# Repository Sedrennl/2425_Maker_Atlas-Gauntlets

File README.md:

# 🛠️ Atlas Gauntlets — Projet Maker 2024–2025

Bienvenue sur le dépôt du projet **Atlas Gauntlets**, une aventure mêlant design, électronique et fabrication numérique, réalisée dans le cadre du module *Maker* de l'année universitaire 2024–2025.
[video youtube de présentation](https://youtu.be/Dz7flcC625o)

## 🎯 Contexte pédagogique

Ce projet s'inscrit dans le cadre du module *Maker* de l'ENSEA, visant à initier les étudiants aux technologies de fabrication numérique, à la conception assistée par ordinateur (CAO) et à l'intégration de systèmes électroniques. L'objectif était de concevoir et de réaliser un objet interactif alliant esthétique et fonctionnalité.

## 🧤 Présentation du projet

Les **Atlas Gauntlets** sont des gantelets inspirés de l'univers de la science-fiction, intégrant des éléments lumineux et des composants électroniques pour offrir une expérience immersive. Le projet a été conçu pour être à la fois visuellement impressionnant et techniquement fonctionnel, avec une attention particulière portée à l'ergonomie et à l'esthétique.

## 🧾 Documentation

Pour une immersion complète dans le projet, consultez le [rapport détaillé]([https://github.com/Sedrennl/2425_Maker_Atlas-Gauntlets/blob/main/rapport.md](https://github.com/Sedrennl/2425_Maker_Atlas-Gauntlets/blob/main/Rapport/rapport.md)), qui couvre :

- **Conception et modélisation 3D** : choix des matériaux, techniques de modélisation, et ajustements pour l'impression 3D.
- **Intégration électronique** : sélection des composants, schémas de câblage, et programmation des effets lumineux.
- **Processus de fabrication** : étapes d'impression, assemblage, et finitions.
- **Tests et itérations** : retours d'expérience, défis rencontrés, et améliorations apportées.

## 📁 Contenu du dépôt

- `rapport.md` : Document détaillant chaque étape du projet, de la conception à la réalisation.
- `models/` : Fichiers STL et sources des modèles 3D utilisés pour l'impression.
- `code/` : Scripts et programmes utilisés pour contrôler les composants électroniques.
- `images/` : Photographies du processus de fabrication et du produit fini.

## 🙏 Remerciements

Un Grand Merci : 

- **M. Papazoglou**
- **Mme Kittel**
- **M. Fiack** 
- **M. Bleimling**

---

N'hésitez pas à explorer les fichiers du dépôt pour en savoir plus sur la réalisation de ce projet passionnant.

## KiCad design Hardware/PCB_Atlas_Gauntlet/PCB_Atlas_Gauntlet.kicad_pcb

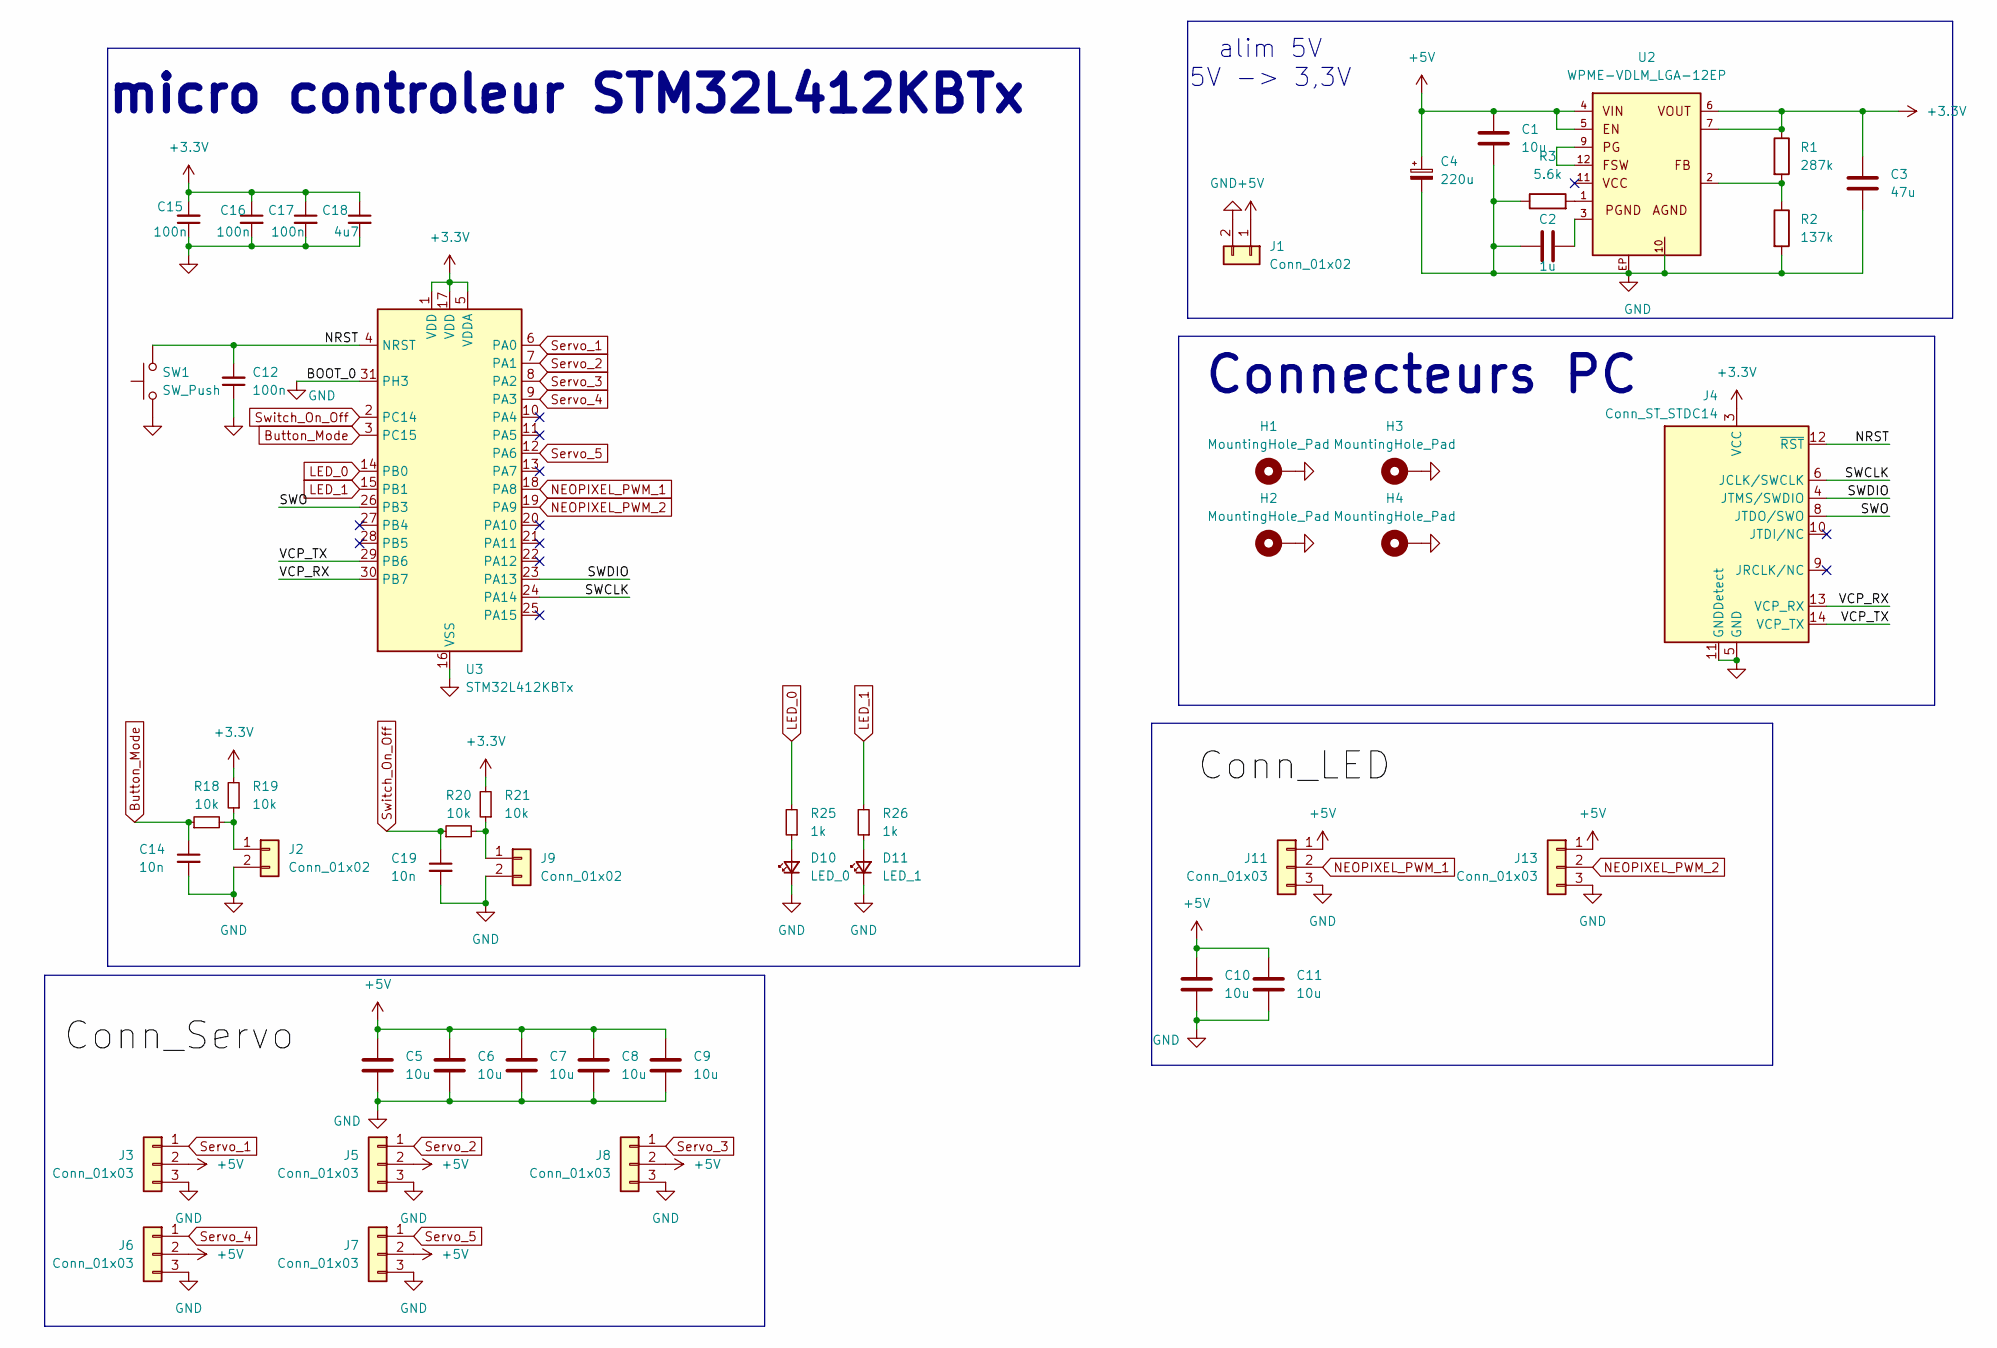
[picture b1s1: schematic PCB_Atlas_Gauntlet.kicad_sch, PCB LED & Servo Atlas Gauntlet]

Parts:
C1, C5, C6, C7, C8, C9, C10, C11: 10u; C_0603_1608Metric; MPN 885 012 106 006
C2: 1u; C_0402_1005Metric
C3: 47u; C_0805_2012Metric; MPN 885 012 107 006
C4: 220u; CP_Elec_8x10.5; MPN 865 060 453 007
C12, C15, C16, C17: 100n; C_0402_1005Metric
C14, C19: 10n; C_0402_1005Metric; MPN WE 885012205050
C18: 4u7; C_0603_1608Metric
D10: LED_0; LED_0603_1608Metric
D11: LED_1; LED_0603_1608Metric
H1, H2, H3, H4: MountingHole_Pad; MountingHole_3.2mm_M3_Pad_Via
J1: Conn_01x02; AMASS_XT30U-F_1x02_P5.0mm_Vertical
J2, J9: Conn_01x02; JST_XH_S2B-XH-A_1x02_P2.50mm_Horizontal
J3, J5, J6, J7, J8, J11, J13: Conn_01x03; JST_XH_B3B-XH-A_1x03_P2.50mm_Vertical
J4: Conn_ST_STDC14; PinHeader_2x07_P1.27mm_Vertical_SMD
R1: 287k; C_0402_1005Metric
R2: 137k; C_0402_1005Metric
R3: 5.6k; C_0402_1005Metric
R18, R19, R20, R21: 10k; R_0402_1005Metric
R25, R26: 1k; R_0402_1005Metric
SW1: SW_Push; SW_Push_1P1T_NO_CK_KSC7xxJ
U2: WPME-VDLM_LGA-12EP; 171021801
U3: STM32L412KBTx; LQFP-32_7x7mm_P0.8mm

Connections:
+3.3V: C3.1, C15.2, C16.1, C17.1, C18.1, J4.3 (VCC), R1.1, R19.2, R21.2, U2.6, U2.7, U3.1 (VDD), U3.5 (VDDA), U3.17 (VDD)
+5V: C1.1, C4.1, C5.1, C6.1, C7.1, C8.1, C9.1, C10.1, C11.1, J1.1, J3.2, J5.2, J6.2, J7.2, J8.2, J11.1, J13.1, U2.4, U2.5
/NRST: C12.2, J4.12 (~RST), SW1.2, U3.4 (NRST)
/SWCLK: J4.6 (JCLK/SWCLK), U3.24 (PA14)
/SWDIO: J4.4 (JTMS/SWDIO), U3.23 (PA13)
/SWO: J4.8 (JTDO/SWO), U3.26 (PB3)
/VCP_RX: J4.13 (VCP_RX), U3.30 (PB7)
/VCP_TX: J4.14 (VCP_TX), U3.29 (PB6)
Button_Mode: C14.1, R18.1, U3.3 (PC15)
GND: C1.2, C2.1, C3.2, C4.2, C5.2, C6.2, C7.2, C8.2, C9.2, C10.2, C11.2, C12.1, C14.2, C15.1, C16.2, C17.2, C18.2, C19.2, D10.1 (K), D11.1 (K), H1.1, H2.1, H3.1, H4.1, J1.2, J2.2, J3.3, J4.5 (GND), J4.7 (GND), J4.11 (GNDDetect), J5.3, J6.3, J7.3, J8.3, J9.2, J11.3, J13.3, R2.2, R3.1, SW1.1, U2.10, U2.EP, U3.16 (VSS), U3.31 (PH3), U3.32 (VSS)
LED_0: R25.2, U3.14 (PB0)
LED_1: R26.2, U3.15 (PB1)
NEOPIXEL_PWM_1: J11.2, U3.18 (PA8)
NEOPIXEL_PWM_2: J13.2, U3.19 (PA9)
unnamed: C2.2, U2.3
unnamed: D10.2 (A), R25.1
unnamed: D11.2 (A), R26.1
unnamed: J2.1, R18.2, R19.1
unnamed: J9.1, R20.2, R21.1
unnamed: R1.2, R2.1, U2.2
unnamed: R3.2, U2.1
unnamed: U2.9, U2.12
Servo_1: J3.1, U3.6 (PA0)
Servo_2: J5.1, U3.7 (PA1)
Servo_3: J8.1, U3.8 (PA2)
Servo_4: J6.1, U3.9 (PA3)
Servo_5: J7.1, U3.12 (PA6)
Switch_On_Off: C19.1, R20.1, U3.2 (PC14)

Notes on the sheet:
alim 5V 5V -> 3,3V
Connecteurs PC
micro controleur STM32L412KBTx

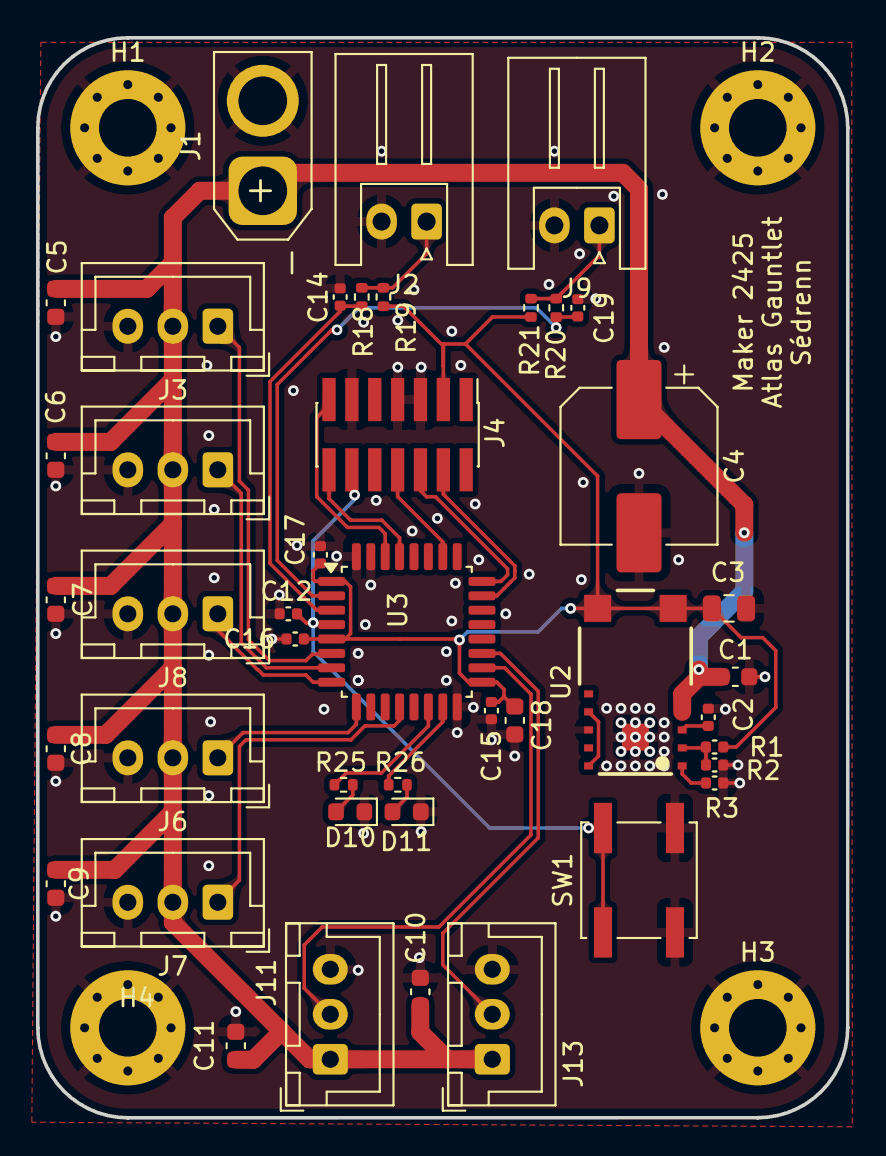
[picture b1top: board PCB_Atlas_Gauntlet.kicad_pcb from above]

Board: 2 copper layers, 45.0 x 60.0 mm, 47 parts (0 on the bottom side), 28 nets.

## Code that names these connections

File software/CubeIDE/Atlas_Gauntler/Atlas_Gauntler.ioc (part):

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Mcu.Name=STM32L412KBTx
Mcu.Package=LQFP32
Mcu.UserName=STM32L412KBTx
PA0-CK_IN.Mode=HSE-External-Clock-Source-for-LittleOrca
PA0-CK_IN.Signal=RCC_CK_IN
PA1.Signal=S_TIM2_CH2
PA10.Signal=S_TIM1_CH3
PA11.Signal=S_TIM1_CH4
PA13\ (JTMS/SWDIO).Signal=SYS_JTMS-SWDIO
PA14\ (JTCK/SWCLK).Signal=SYS_JTCK-SWCLK
PA15\ (JTDI).Signal=SYS_JTDI
PA2.Signal=S_TIM2_CH3
PA3.Signal=S_TIM2_CH4
PA5.Signal=S_TIM2_CH1
PA8.Signal=S_TIM1_CH1
PA9.Signal=S_TIM1_CH2
PC14-OSC32_IN\ (PC14).Signal=GPIO_Output
PC15-OSC32_OUT\ (PC15).Signal=GPIO_Output
PH3-BOOT0\ (BOOT0).Signal=GPIO_Input
RCC.HSE_VALUE=8000000
board=custom

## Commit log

2024-12-21 Create Ref
2024-12-21 Rename Ref to Ref.md
2025-01-14 added ref
2025-01-14 Rename Capture d'écran 2024-12-21 192545.png to vibe.png
2025-01-16 photos
2025-01-27 add slides cours
2025-01-27 cgt emplacement fichier
2025-01-27 cgtemplacement
2025-03-24 blabla
2025-03-24 fix schematic
2025-03-24 MAJ_PCB
2025-03-24 MAJ PCB
2025-03-31 kjfv
2025-04-24 MAJ rapport
